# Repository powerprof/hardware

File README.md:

# PowerProf Hardware Resources

PowerProf is a current monitor for embedded systems. You can use it to get accurate current consumption data for any workload or operating conditions, and then use that information to design battery-based systems with just the right amount of capacity.

There are currently three supported microcontrollers - the Teensy 3.6, the LOLIN D1 Mini, and the LOLIN D32. The Teensy version supports communication over USB, the LOLIN D1 Mini supports USB and WiFi, and the LOLIN D32 supports USB, WiFi, and BLE. All boards use the [INA260 current sensor](https://www.ti.com/lit/ds/symlink/ina260.pdf) from Texas Instruments. There are two variants of the LOLIN D1 Mini board - one uses the INA260 breakout board from Adafruit, and the other uses an INA260 directly.

## Protocol Support

| Board   | USB | WiFi | BLE |
| ------- | --- | ---- | --- |
| Teensy  | Yes | No   | No  |
| D1 Mini | Yes | Yes  | No  |
| D32     | Yes | Yes  | Yes |

## Specifications

| Name                | Absolute         | Typical      |
| ------------------- | ---------------- | ------------ |
| Measurement Voltage | -0.3V - 40V      | 0 - 36V      |
| Measurement Current | 0 - 15A          | 0 - 10A      |
| Voltage Resolution  | 1.25mV           |              |
| Current Resolution  | 1.25mA           |              |
| Power Resolution    | 10mW             |              |
| Sample Rate         | 110Hz - 6.494kHz | 110Hz - 1kHz |
| Supply Voltage      | 5V               | 5V           |
| Supply Current      | 30-500mA         | 100mA[^1]    |

[^1]: Depends on which board and protocol is in use.

## Wiring Diagrams

## Teensy

The Teensy board is a carrier board which houses the microcontroller and the INA260 current sensor.

[Order this board from OSH Park](https://oshpark.com/shared_projects/yNJN1VsL)

### Schematic

### Board

### BOM

| Mfg      | Name                | Qty | Buy                                                                                                           |
| -------- | ------------------- | --- | ------------------------------------------------------------------------------------------------------------- |
| PJRC     | Teensy 3.6          | 1   | [Link](https://www.pjrc.com/store/teensy36.html)                                                              |
| Adafruit | INA260 Breakout     | 1   | [Link](https://www.mouser.com/ProductDetail/Adafruit/4226?qs=PzGy0jfpSMvb8foRR1BpJA%3D%3D)                    |
| TE Conn. | 282834-2            | 1   | [Link](https://www.mouser.com/ProductDetail/TE-Connectivity/282834-2?qs=A%252Bip%252BNCYi6N8cVKuk8xDog%3D%3D) |
| DuPont   | 8-pin 2.54mm Header | 1   |                                                                                                               |

### Assembly

1. Solder the Teensy to the top side of the board.
2. Solder the 8-pin header to the top side of the board.
3. Solder the INA260 to the 8-pin header.
4. Solder the terminal block to the top side of the board.

## LOLIN D1 Mini

### r1 - INA260 Breakout

This board is a "shield" for the D1 Mini which has an INA260 breakout board mounted on it.

[Order this board from OSH Park](https://oshpark.com/shared_projects/ZZhTuBfp)

#### Schematic

#### Board

#### BOM

| Mfg      | Name                            | Qty | Buy                                                                                        |
| -------- | ------------------------------- | --- | ------------------------------------------------------------------------------------------ |
| LOLIN    | D1 Mini                         | 1   | [Link](https://www.wemos.cc/en/latest/d1/d1_mini.html)                                     |
| Adafruit | INA260 Breakout                 | 1   | [Link](https://www.mouser.com/ProductDetail/Adafruit/4226?qs=PzGy0jfpSMvb8foRR1BpJA%3D%3D) |
| DuPont   | 8-pin 2.54mm Header             | 2   |                                                                                            |
| DuPont   | 6-pin 2.54mm Header             | 1   |                                                                                            |
| DuPont   | 2-pin Right Angle 2.54mm Header | 1   |                                                                                            |

#### Assembly

1. Solder the two 8-pin headers on the underside of the board.
2. Solder the 6-pin header to the top side of the board.
3. Solder the 2-pin right angle header to the top side of the board.
4. Solder the INA260 to the 6-pin header - make sure that V+/V- pins of the INA260 breakout are not connected!
5. Install the shield on top of a D1 Mini.

### r2 - INA260 Onboard

This board is a "shield" for the D1 Mini which has an INA260 directly soldered to it.

[Order this board from OSH Park](https://oshpark.com/shared_projects/TSTmxFWv)

#### Schematic

#### Board

#### BOM

| Mfg      | Name                | Qty | Buy                                                                                        |
| -------- | ------------------- | --- | ------------------------------------------------------------------------------------------ |
| LOLIN    | D1 Mini             | 1   | [Link](https://www.wemos.cc/en/latest/d1/d1_mini.html)                                     |
| Adafruit | INA260 Breakout     | 1   | [Link](https://www.mouser.com/ProductDetail/Adafruit/4226?qs=PzGy0jfpSMvb8foRR1BpJA%3D%3D) |
| DuPont   | 8-pin 2.54mm Header | 2   |                                                                                            |
| TI       | INA260AIPWR         | 1   | [Link](https://www.mouser.com/ProductDetail/595-INA260AIPWR)                               |
| Bourns   | CR0201AFW-1002GAS   | 4   | [Link](https://www.mouser.com/ProductDetail/652-CR0201AFW1002GAS)                          |
| Samsung  | CL03A105MQ3CSNH     | 1   | [Link](https://www.mouser.com/ProductDetail/187-CL03A105MQ3CSNH)                           |

#### Assembly

1. Solder the INA260 and the SMD resistors/capacitor to the top side of the board.
2. Solder the two 8-pin headers to the underside of the board.
3. Solder the 4-pin terminal block to the top side of the board.
4. Install the shield on top of a D1 Mini.

## LOLIN D32

This is a carrier board which houses the microcontroller and the INA260 current sensor.

[Order this board from OSH Park](https://oshpark.com/shared_projects/jJYH4pyw)

### Schematic

### Board

### BOM

| Mfg      | Name                | Qty | Buy                                                                                                           |
| -------- | ------------------- | --- | ------------------------------------------------------------------------------------------------------------- |
| LOLIN    | D32                 | 1   | [Link](https://www.aliexpress.com/item/32808551116.html)                                                      |
| Adafruit | INA260 Breakout     | 1   | [Link](https://www.mouser.com/ProductDetail/Adafruit/4226?qs=PzGy0jfpSMvb8foRR1BpJA%3D%3D)                    |
| TE Conn. | 282834-2            | 1   | [Link](https://www.mouser.com/ProductDetail/TE-Connectivity/282834-2?qs=A%252Bip%252BNCYi6N8cVKuk8xDog%3D%3D) |
| DuPont   | 8-pin 2.54mm Header | 1   |                                                                                                               |

### Assembly

1. Solder the D32 to the top side of the board.
2. Solder the 8-pin header to the top side of the board.
3. Solder the INA260 breakout to the 8-pin header.
4. Solder the 2-pin terminal block to the top side of the board.

## Roadmap

Some things we'd like to add, given the time:

- One modular connector for the front-end instead of four separate wires

## Acknowledgements

Special thanks to [weeding-nerdy](https://github.com/weeding-nerdy) for their [gufu_gud](https://github.com/weeding-nerdy/gufu_gud), which was the inspiration for this project.

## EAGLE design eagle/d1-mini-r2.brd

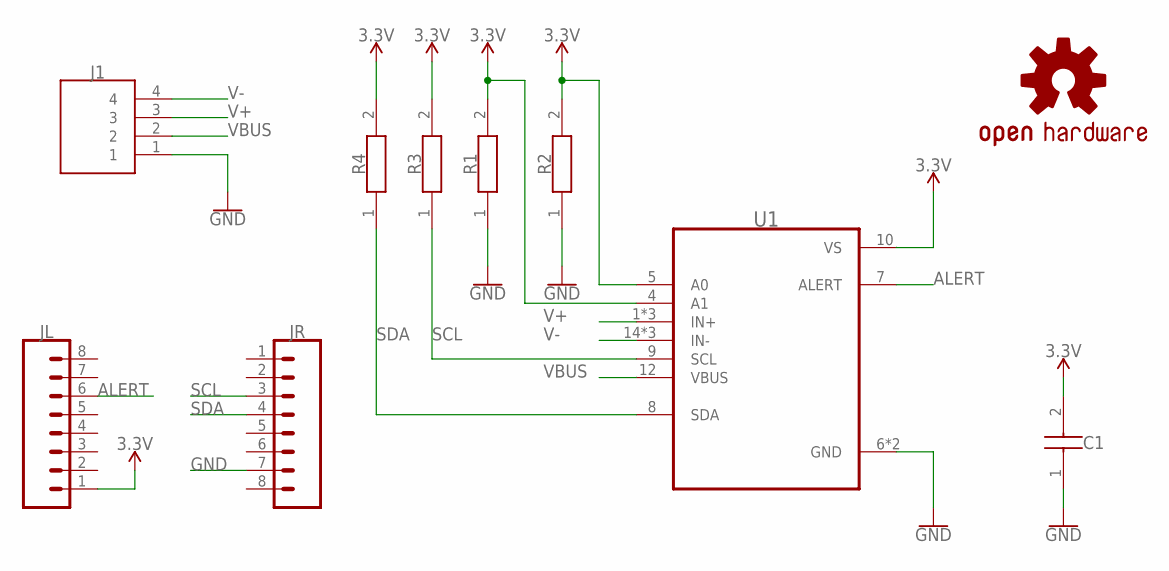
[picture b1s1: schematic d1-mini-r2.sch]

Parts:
C1: CL03A105MQ3CSNH; CAPC1608X80N
J1: 282834-4; 2828344
JL: CONN_08NO_SILK_FEMALE_PTH; 1X08_NO_SILK
JR: CONN_08NO_SILK_FEMALE_PTH; 1X08_NO_SILK
LOGO1: OSHW-LOGOS; OSHW-LOGO-S
R1, R2, R3, R4: CRCW020110K0FNED; RESC0603X28N
U1: INA260AIPWR; SOP65P640X120-16N

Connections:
3.3V: C1.2, JL.1, R1.2, R2.2, R3.2, R4.2, U1.4 (A1), U1.5 (A0), U1.10 (VS)
ALERT: JL.6, U1.7 (ALERT)
GND: C1.1, J1.1, JR.7, R1.1, R2.1, U1.6 (GND), U1.11 (GND)
SCL: JR.3, R3.1, U1.9 (SCL)
SDA: JR.4, R4.1, U1.8 (SDA)
V+: J1.3, U1.1 (IN+), U1.2 (IN+), U1.3 (IN+)
V-: J1.4, U1.14 (IN-), U1.15 (IN-), U1.16 (IN-)
VBUS: J1.2, U1.12 (VBUS)

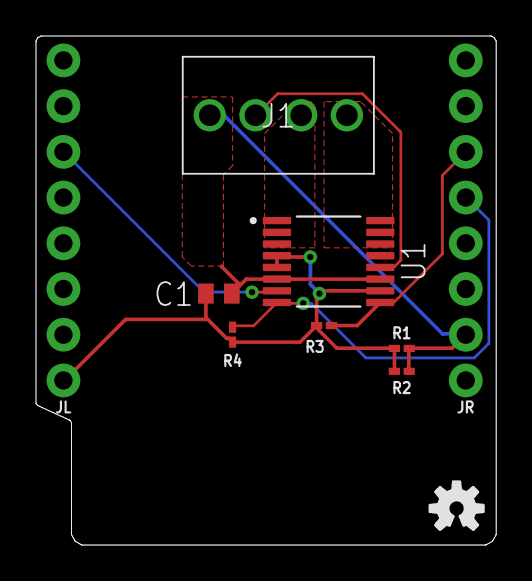
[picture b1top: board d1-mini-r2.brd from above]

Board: 2 copper layers, 25.6 x 28.3 mm, 10 parts (0 on the bottom side), 8 nets.

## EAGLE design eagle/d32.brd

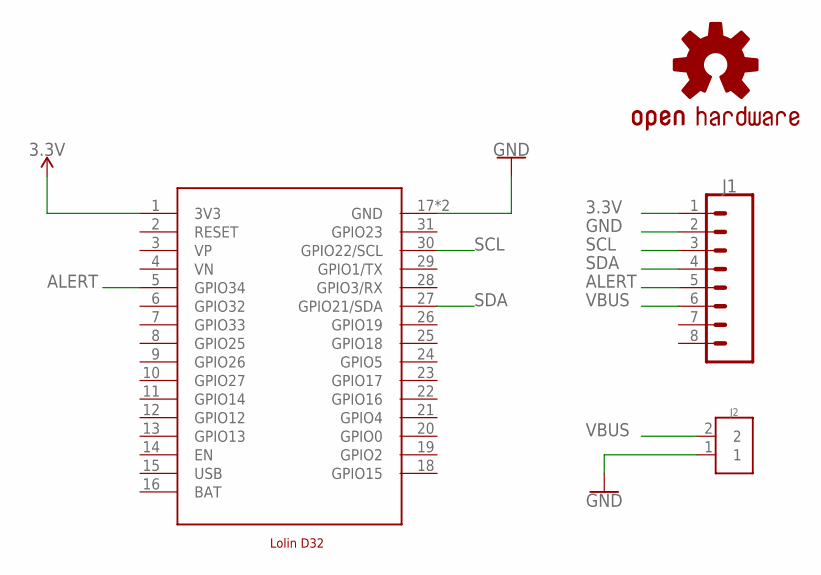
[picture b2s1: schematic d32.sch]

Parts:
J1: CONN_08NO_SILK_FEMALE_PTH; 1X08_NO_SILK
J2: 282834-2; CONN_282834-2
LOGO1: OSHW-LOGOS; OSHW-LOGO-S
U1: LOLIND32

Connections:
3.3V: J1.1, U1.1 (3V3)
ALERT: J1.5, U1.5 (GPIO34)
BAT: U1.16 (BAT)
GND: J1.2, J2.1, U1.17 (GND), U1.32 (GND)
SCL: J1.3, U1.30 (GPIO22/SCL)
SDA: J1.4, U1.27 (GPIO21/SDA)
USB: U1.15 (USB)
VBUS: J1.6, J2.2

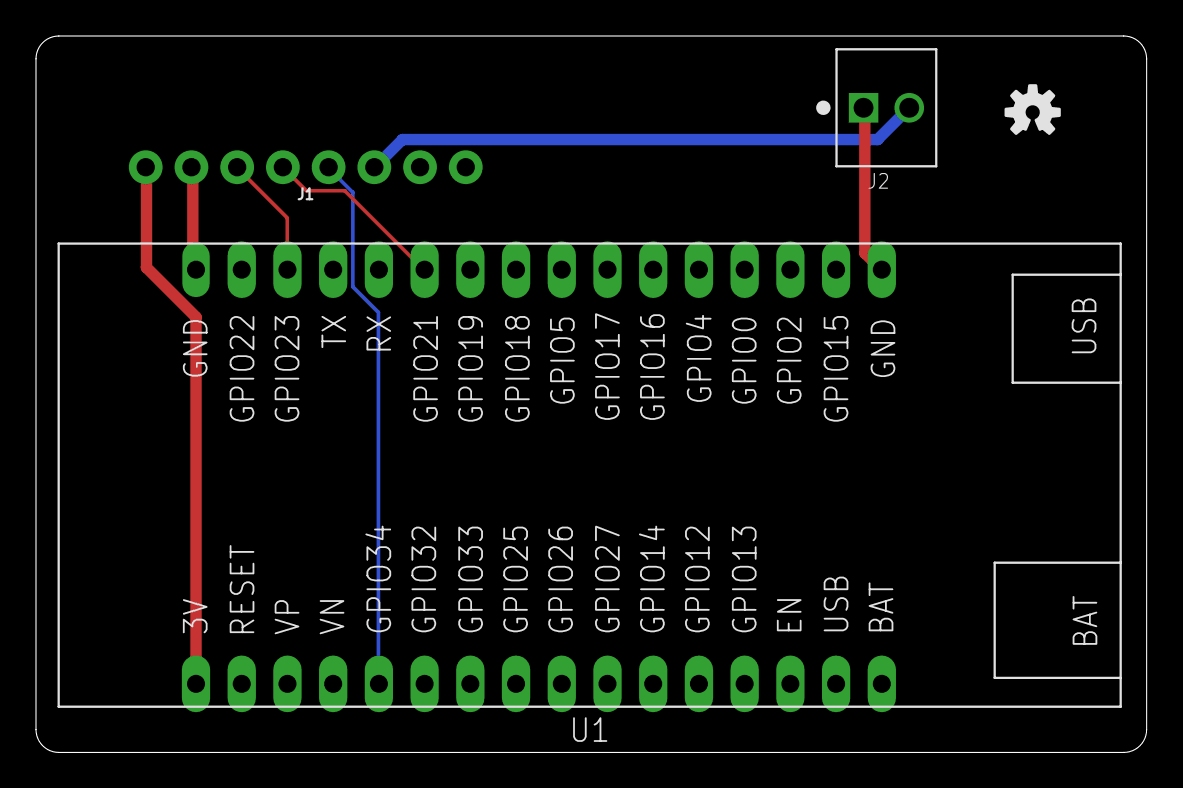
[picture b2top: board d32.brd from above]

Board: 2 copper layers, 61.7 x 39.8 mm, 4 parts (0 on the bottom side), 6 nets.

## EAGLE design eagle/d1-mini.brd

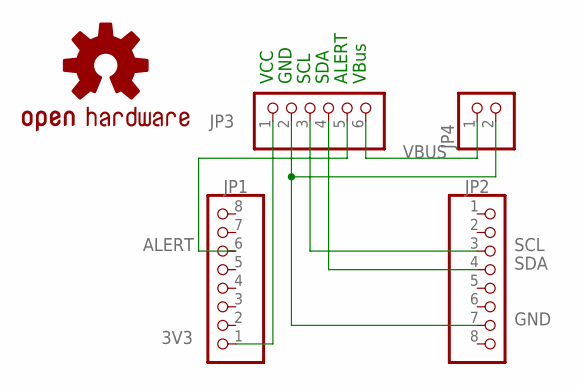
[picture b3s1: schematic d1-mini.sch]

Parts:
JP1, JP2: PINHD-1X8; 1X08
JP3: PINHD-1X6; 1X06
JP4: PINHD-1X2/90; 1X02/90
LOGO1: OSHW-LOGOS; OSHW-LOGO-S

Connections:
3V3: JP1.1, JP3.1
ALERT: JP1.6, JP3.5
GND: JP2.7, JP3.2, JP4.2
SCL: JP2.3, JP3.3
SDA: JP2.4, JP3.4
VBUS: JP3.6, JP4.1

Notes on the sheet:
VCC
GND
SCL
SDA
ALERT
VBus

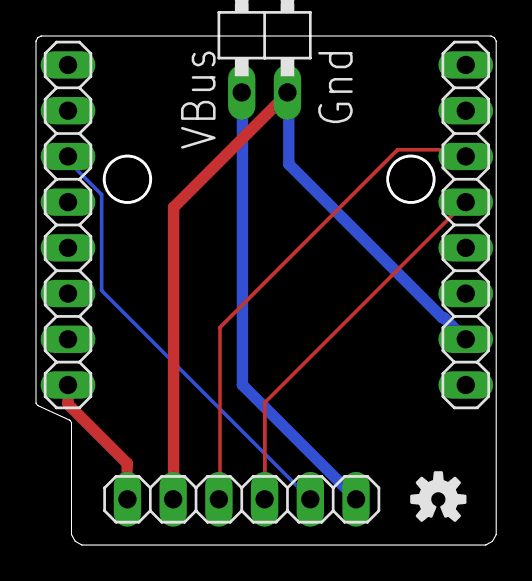
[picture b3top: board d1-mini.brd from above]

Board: 2 copper layers, 25.4 x 28.1 mm, 5 parts (0 on the bottom side), 6 nets.

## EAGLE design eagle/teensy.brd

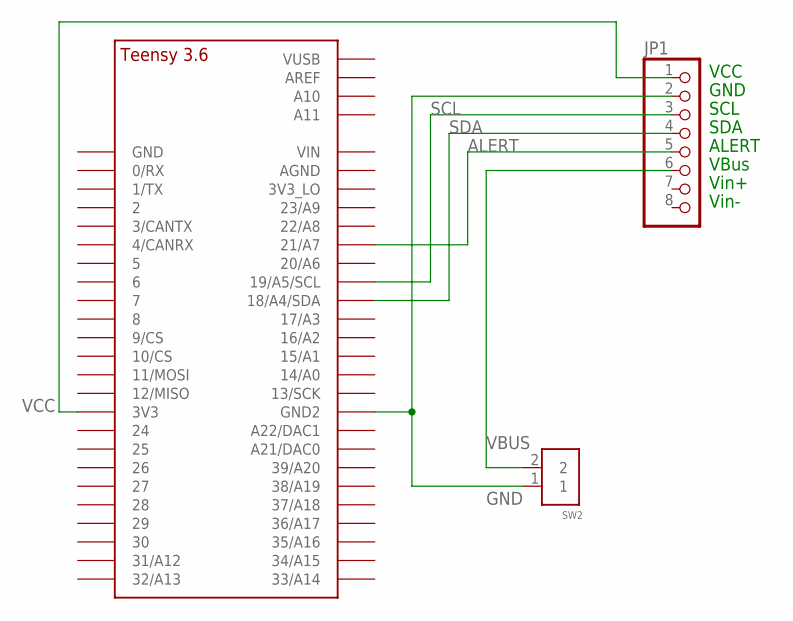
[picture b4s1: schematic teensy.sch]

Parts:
JP1: PINHD-1X8; 1X08
SW2: 282834-2; CONN_282834-2
U1: TEENSY_3.5/3.6_BASIC

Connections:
ALERT: JP1.5, U1.21/A7
GND: JP1.2, SW2.1, U1.GND2
SCL: JP1.3, U1.19/A5/SCL
SDA: JP1.4, U1.18/A4/SDA
VBUS: JP1.6, SW2.2
VCC: JP1.1, U1.3V3

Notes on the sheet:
VCC
GND
SCL
SDA
ALERT
VBus
Vin+
Vin-

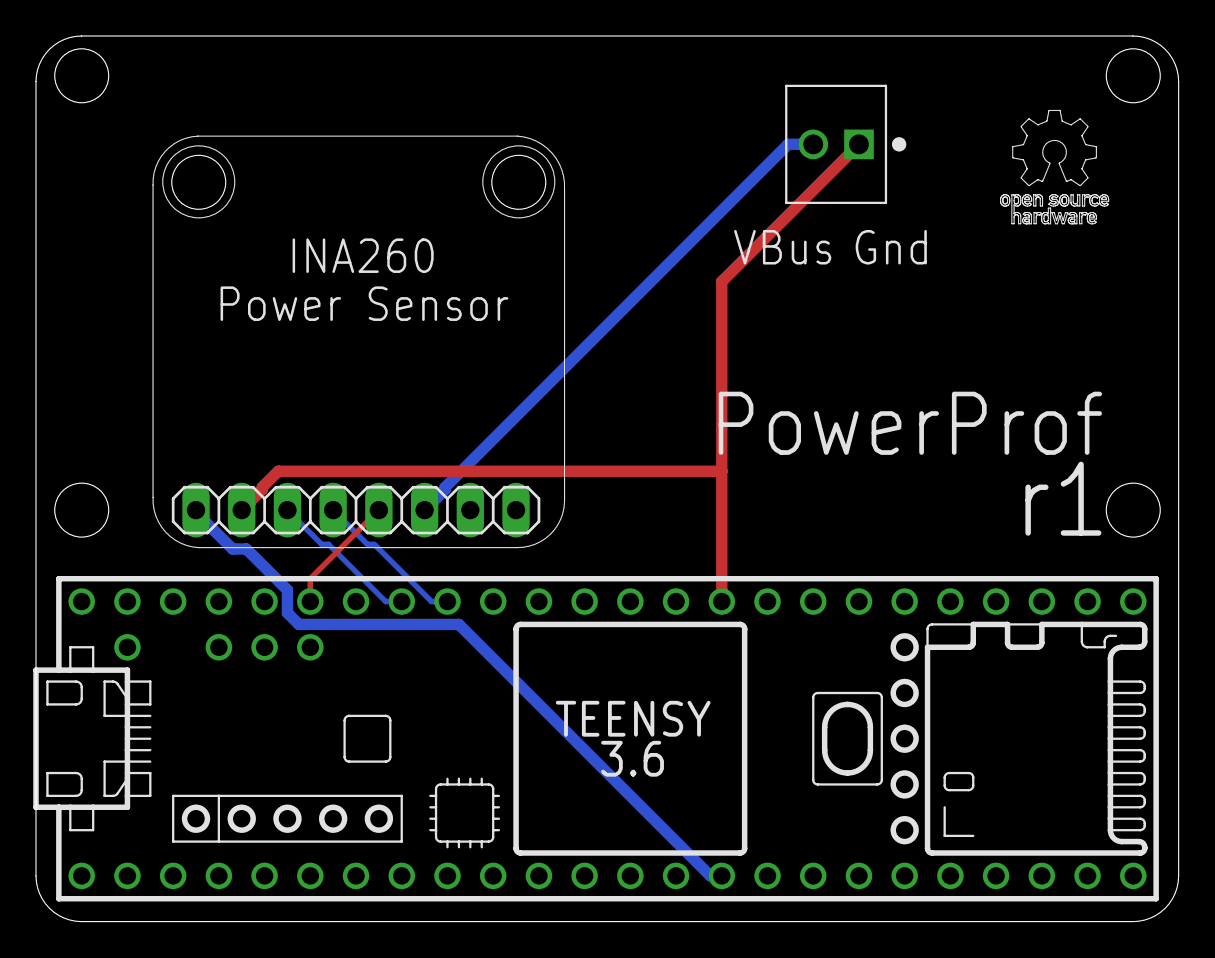
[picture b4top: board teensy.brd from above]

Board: 2 copper layers, 63.5 x 49.2 mm, 3 parts (0 on the bottom side), 6 nets.

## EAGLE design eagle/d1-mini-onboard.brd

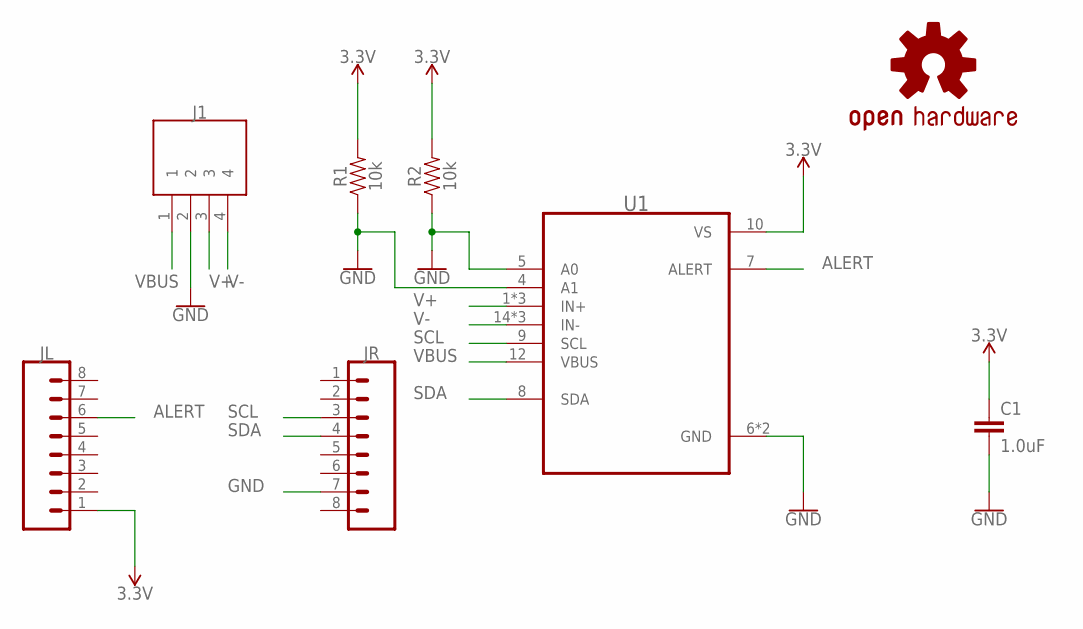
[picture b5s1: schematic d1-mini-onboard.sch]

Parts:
C1: 1.0uF; 1206
J1: 282834-4; 2828344
JL: CONN_08NO_SILK_FEMALE_PTH; 1X08_NO_SILK
JR: CONN_08NO_SILK_FEMALE_PTH; 1X08_NO_SILK
LOGO1: OSHW-LOGOS; OSHW-LOGO-S
R1, R2: 10k; 1206
U1: INA260AIPWR; SOP65P640X120-16N

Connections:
3.3V: C1.1, JL.1, R1.2, R2.2, U1.10 (VS)
ALERT: JL.6, U1.7 (ALERT)
GND: C1.2, J1.2, JR.7, R1.1, R2.1, U1.4 (A1), U1.5 (A0), U1.6 (GND), U1.11 (GND)
SCL: JR.3, U1.9 (SCL)
SDA: JR.4, U1.8 (SDA)
V+: J1.3, U1.1 (IN+), U1.2 (IN+), U1.3 (IN+)
V-: J1.4, U1.14 (IN-), U1.15 (IN-), U1.16 (IN-)
VBUS: J1.1, U1.12 (VBUS)

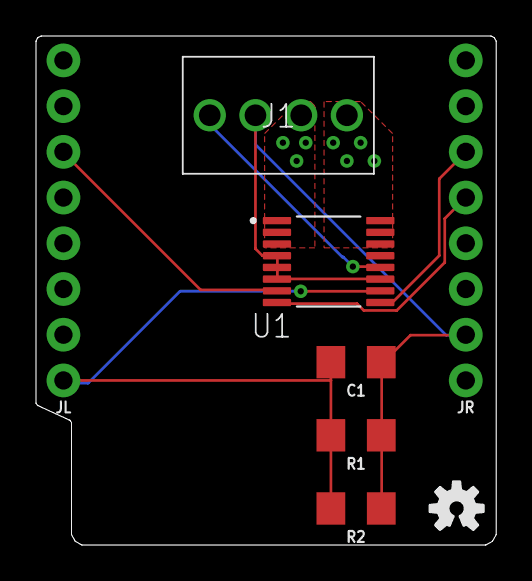
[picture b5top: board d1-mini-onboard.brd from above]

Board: 2 copper layers, 25.6 x 28.3 mm, 8 parts (0 on the bottom side), 8 nets.

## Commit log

2021-09-13 add documentation and EAGLE files for teensy and d1 mini boards
2021-09-14 switch d1-mini eagle board to use 2.54mm pin header for vbus/gnd and add text/oshw logo
2021-09-17 add MIT license
2021-09-17 add eagle libraries for Teensy board
2021-09-17 add osh park project links
2021-09-17 add acknowledgements
2021-09-17 add roadmap to README.md
2021-09-18 update and sync all schematics and images - fix labels and add consistent attribution
2021-09-18 add specifications and assembly instructions to README.md
2021-10-01 add eagle files for D1 mini "onboard" variant
2021-10-01 clarify that we are talking about board side
2021-10-01 expand on intro paragraph
2021-10-01 add documentation for D1 mini onboard variant
2021-10-05 add skeleton LOLIN D32 support
2021-10-05 add protocol support matrix to README.md
2021-10-05 add footnote about typical current
2021-10-05 update wiring diagram for BLE
2021-10-06 add top/bottom layers to board images
2021-10-06 add d32 board/schematic/bom/assembly to README.md
2021-10-17 update OSH Park link for Teensy board
2021-10-30 update clearances to 8mil (thanks tech-tx!)
2021-10-30 add d32 board
2021-10-30 remove broken d1-mini-onboard
2021-10-30 remove d1-mini-r2 images until they are fixed
2021-10-30 sync boards to use same net classes, update images with new traces
2021-10-30 update OSH Park links with updated clearances
2021-11-05 re-add d1-mini-r2
2021-11-06 update BOM with new cap/res

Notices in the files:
eagle/d1-mini-onboard.brd:
MIT License - by ayan4m1
parts and their libraries:
SparkFun-Connectors: Licensing: Creative Commons ShareAlike 4.0 International - https://creativecommons.org/licenses/by-sa/4.0
